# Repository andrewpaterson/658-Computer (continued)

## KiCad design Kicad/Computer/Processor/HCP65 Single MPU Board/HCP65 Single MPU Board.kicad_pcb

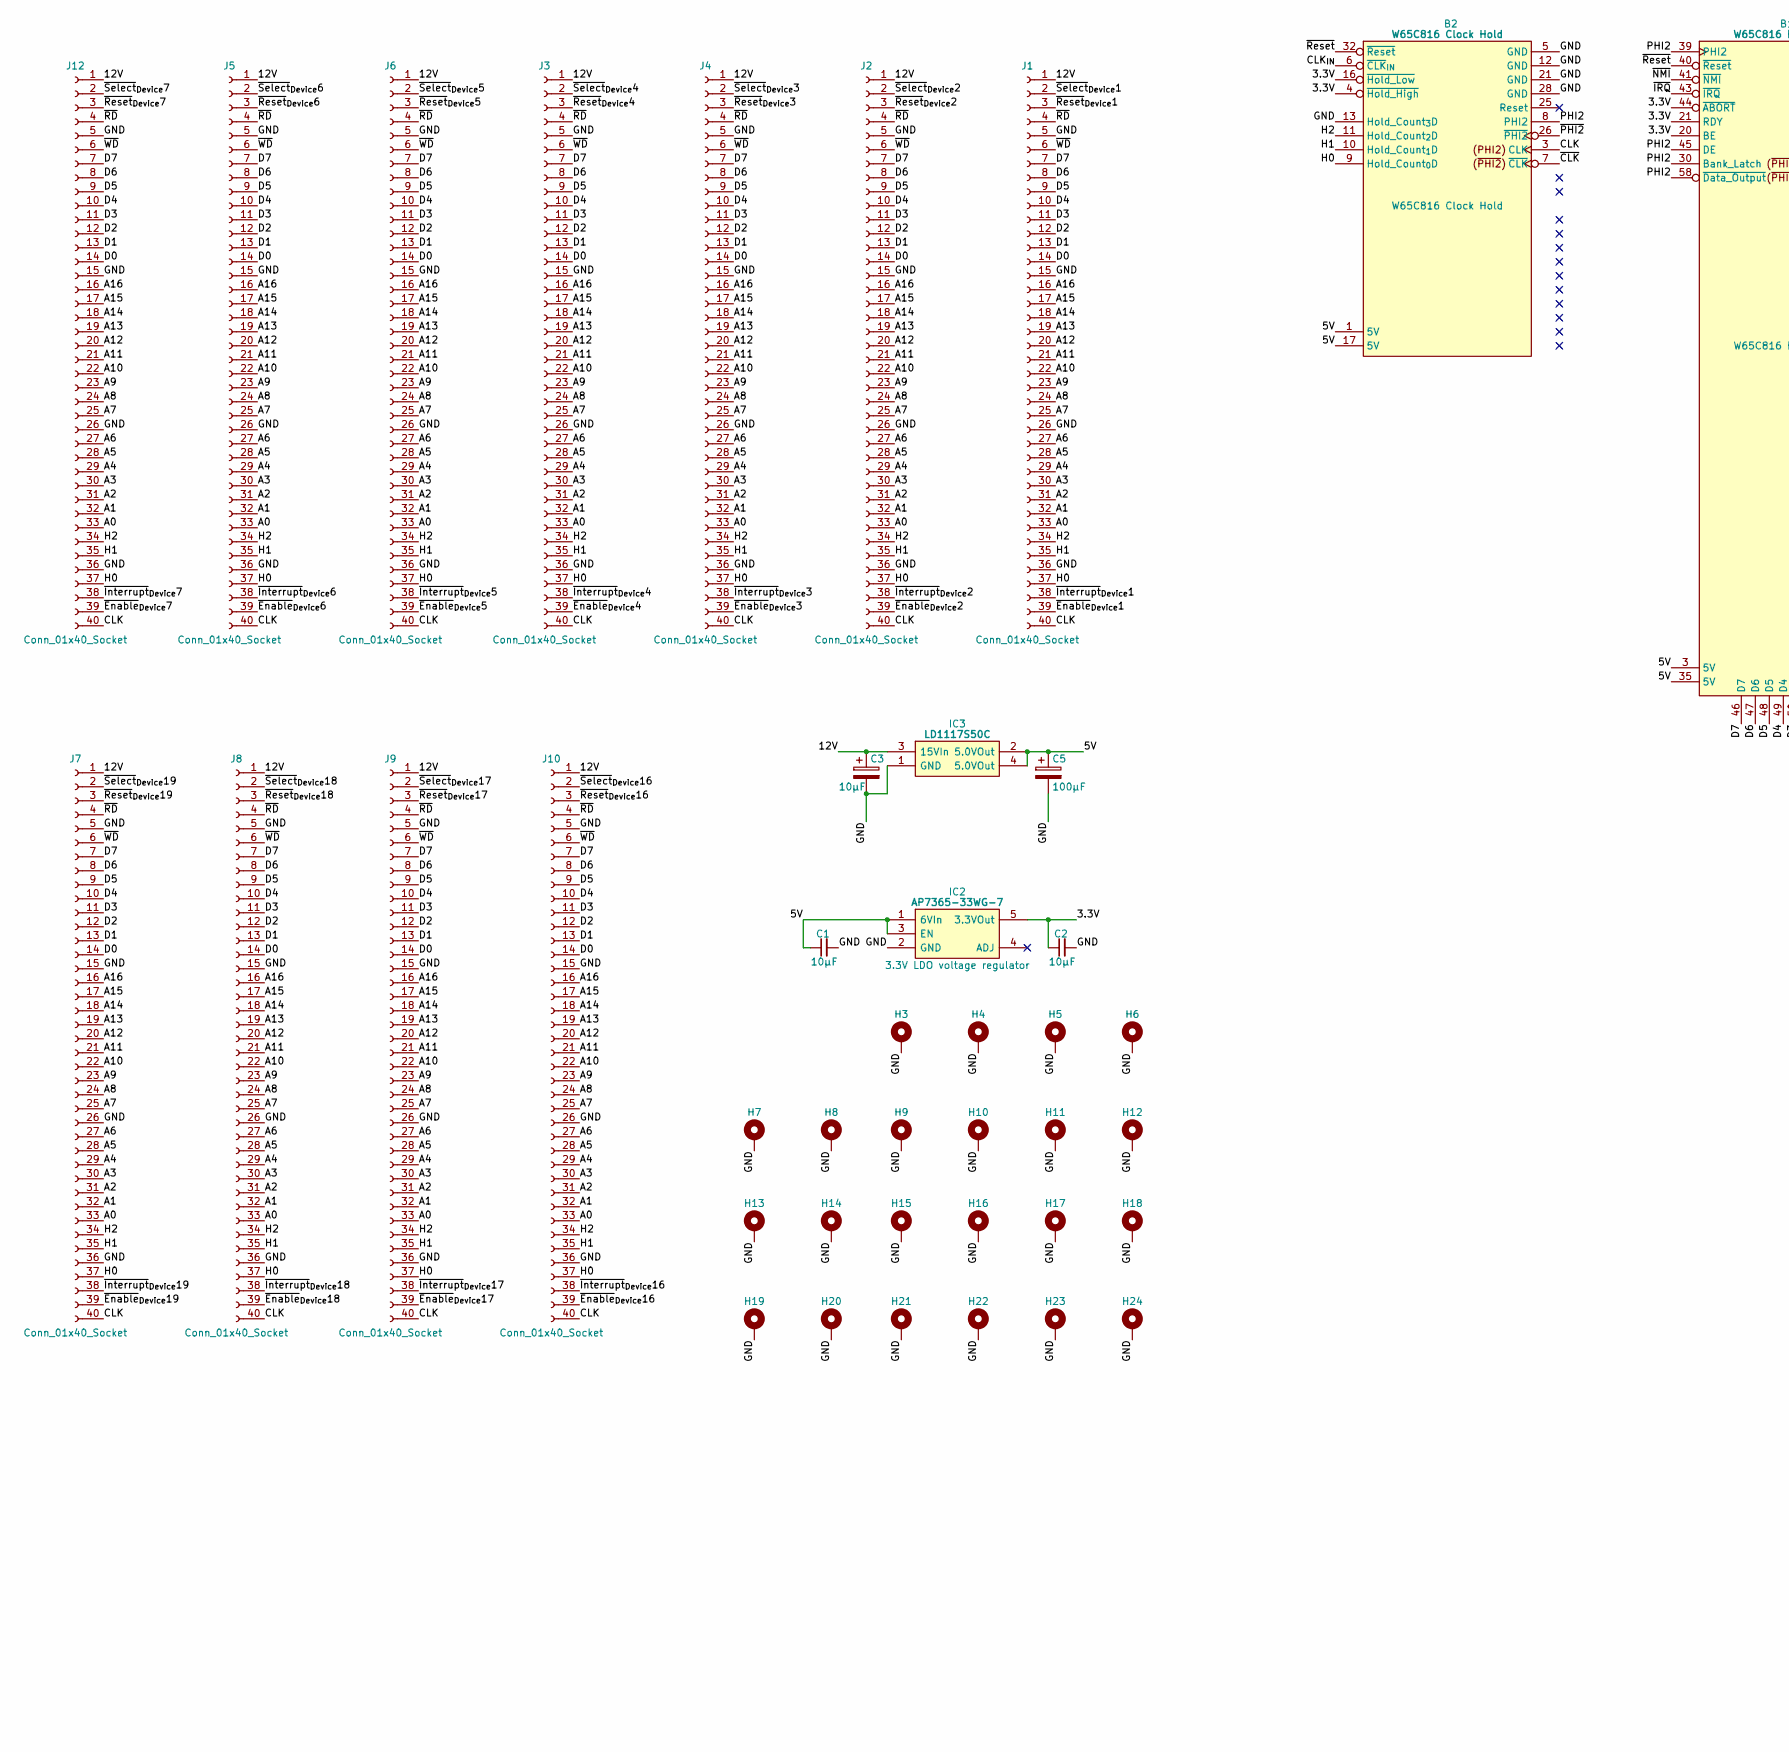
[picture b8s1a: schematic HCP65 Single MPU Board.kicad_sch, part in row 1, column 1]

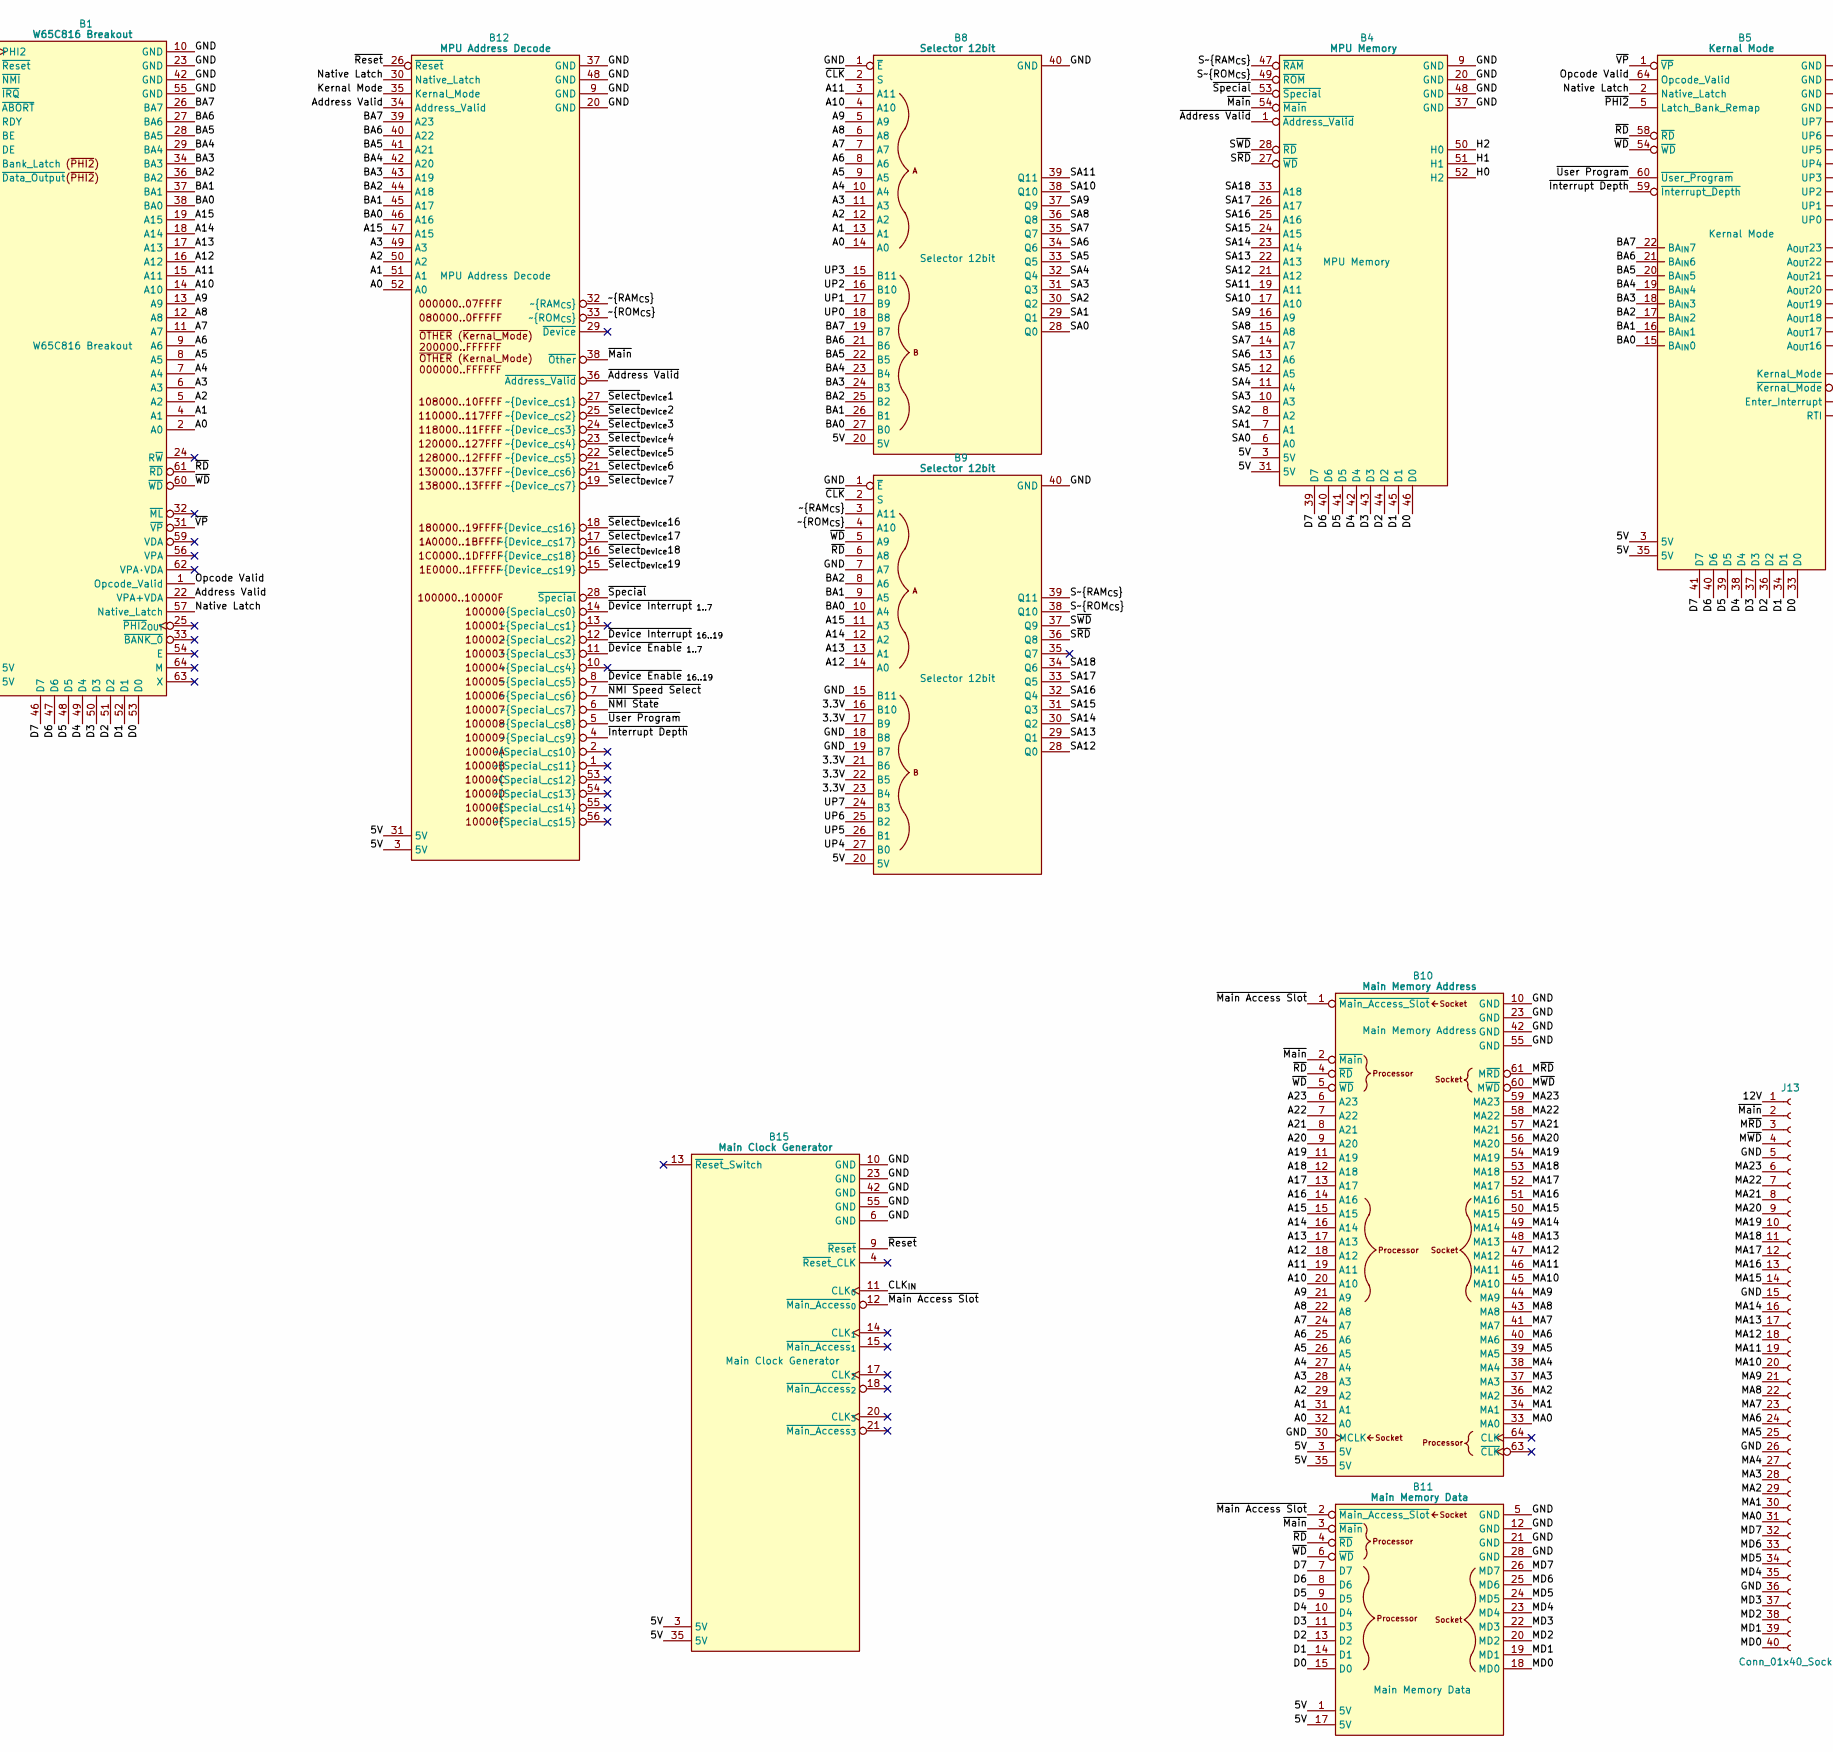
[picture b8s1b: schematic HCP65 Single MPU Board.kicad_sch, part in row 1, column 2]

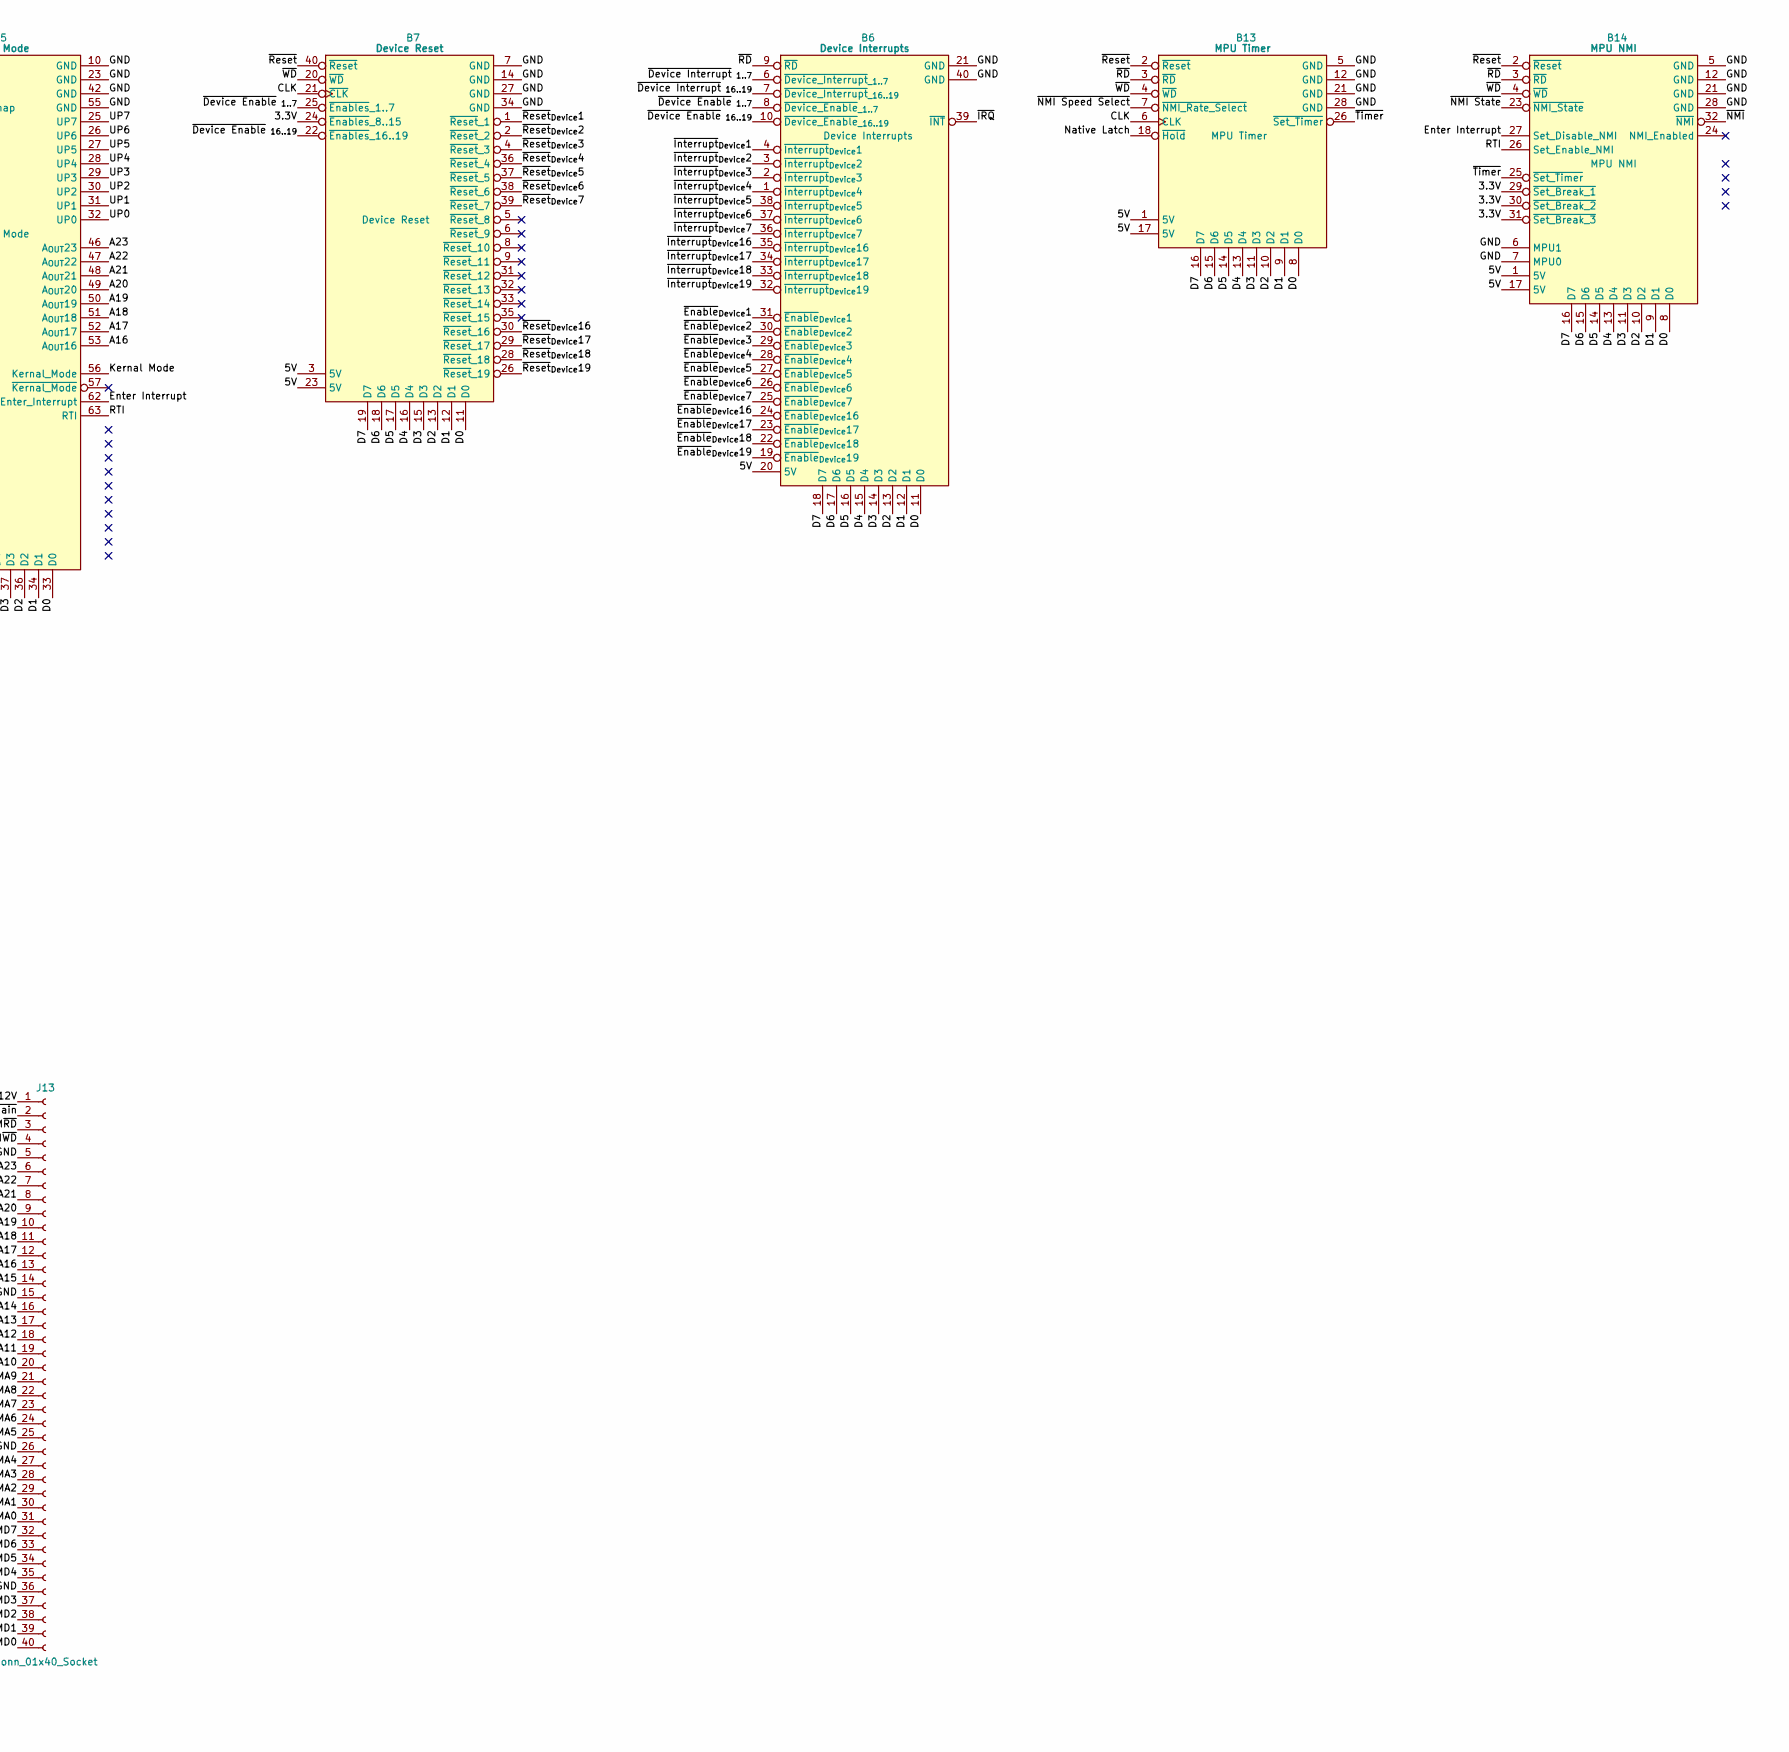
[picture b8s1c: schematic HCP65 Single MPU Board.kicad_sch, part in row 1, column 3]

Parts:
B1: W65C816 Breakout; HCP65_W65C816_Breakout
B2: W65C816 Clock Hold; HCP65_W65C816_Clock_Hold
B4: MPU Memory; HCP65_MPU_Memory
B5: Kernal Mode; HCP65_Kernal_Mode
B6: Device Interrupts; HCP65_Device_Interrupts
B7: Device Reset; HCP65_Device_Reset
B8, B9: Selector 12bit; HCP65_Selector_12bit
B10: Main Memory Address; HCP65_Main_Memory_Address
B11: Main Memory Data; HCP65_Main_Memory_Data
B12: MPU Address Decode; HCP65_MPU_Address_Decode
B13: MPU Timer; HCP65_MPU_Timer
B14: MPU NMI; HCP65_MPU_NMI
B15: Main Clock Generator; HCP65_Clock_Generator
C1, C2: 10µF; C_0805
C3: 10μF; CP_Radial_D4.0mm_P2.00mm
C5: 100μF; CP_Radial_D4.0mm_P2.00mm
H3, H4, H5, H6, H7, H8, H9, H10, H11, H12, H13, H14, H15, H16, H17, H18, H19, H20, H21, H22, H23, H24: MountingHole_Pad; HCP65_MountingHole_M3_
IC2: AP7365-33WG-7; SOT95P285X130-5N; Manufacturer_Part_Number AP7365-33WG-7; Mouser Part Number 621-AP7365-33WG-7
IC3: LD1117S50C; LD1117S33C; Manufacturer_Part_Number LD1117S50C
J1, J2, J3, J4, J5, J6, J7, J8, J9, J10, J12, J13: Conn_01x40_Socket

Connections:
/3.3V: B1.20 (BE), B1.21 (RDY), B1.44 (~ABORT), B2.4 (~Hold_High), B2.16 (~Hold_Low), B7.24 (~Enables_8..15), B9.16 (B10), B9.17 (B9), B9.21 (B6), B9.22 (B5), B9.23 (B4), B14.29 (~Set_Break_1), B14.30 (~Set_Break_2), B14.31 (~Set_Break_3), C2.1, IC2.5 (3.3VOut)
/5V: B1.3 (5V), B1.35 (5V), B2.1 (5V), B2.17 (5V), B4.3 (5V), B4.31 (5V), B5.3 (5V), B5.35 (5V), B6.20 (5V), B7.3 (5V), B7.23 (5V), B8.20 (5V), B9.20 (5V), B10.3 (5V), B10.35 (5V), B11.1 (5V), B11.17 (5V), B12.3 (5V), B12.31 (5V), B13.1 (5V), B13.17 (5V), B14.1 (5V), B14.17 (5V), B15.3 (5V), B15.35 (5V), C1.1, C5.1, IC2.1 (6VIn), IC2.3 (EN), IC3.2 (5.0VOut), IC3.4 (5.0VOut)
/12V: C3.1, IC3.3 (15VIn), J1.1, J2.1, J3.1, J4.1, J5.1, J6.1, J7.1, J8.1, J9.1, J10.1, J12.1, J13.1
/A0: B1.2 (A0), B8.14 (A0), B10.32 (A0), B12.52 (A0), J1.33, J2.33, J3.33, J4.33, J5.33, J6.33, J7.33, J8.33, J9.33, J10.33, J12.33
/A1: B1.4 (A1), B8.13 (A1), B10.31 (A1), B12.51 (A1), J1.32, J2.32, J3.32, J4.32, J5.32, J6.32, J7.32, J8.32, J9.32, J10.32, J12.32
/A2: B1.5 (A2), B8.12 (A2), B10.29 (A2), B12.50 (A2), J1.31, J2.31, J3.31, J4.31, J5.31, J6.31, J7.31, J8.31, J9.31, J10.31, J12.31
/A3: B1.6 (A3), B8.11 (A3), B10.28 (A3), B12.49 (A3), J1.30, J2.30, J3.30, J4.30, J5.30, J6.30, J7.30, J8.30, J9.30, J10.30, J12.30
/A4: B1.7 (A4), B8.10 (A4), B10.27 (A4), J1.29, J2.29, J3.29, J4.29, J5.29, J6.29, J7.29, J8.29, J9.29, J10.29, J12.29
/A5: B1.8 (A5), B8.9 (A5), B10.26 (A5), J1.28, J2.28, J3.28, J4.28, J5.28, J6.28, J7.28, J8.28, J9.28, J10.28, J12.28
/A6: B1.9 (A6), B8.8 (A6), B10.25 (A6), J1.27, J2.27, J3.27, J4.27, J5.27, J6.27, J7.27, J8.27, J9.27, J10.27, J12.27
/A7: B1.11 (A7), B8.7 (A7), B10.24 (A7), J1.25, J2.25, J3.25, J4.25, J5.25, J6.25, J7.25, J8.25, J9.25, J10.25, J12.25
/A8: B1.12 (A8), B8.6 (A8), B10.22 (A8), J1.24, J2.24, J3.24, J4.24, J5.24, J6.24, J7.24, J8.24, J9.24, J10.24, J12.24
/A9: B1.13 (A9), B8.5 (A9), B10.21 (A9), J1.23, J2.23, J3.23, J4.23, J5.23, J6.23, J7.23, J8.23, J9.23, J10.23, J12.23
/A10: B1.14 (A10), B8.4 (A10), B10.20 (A10), J1.22, J2.22, J3.22, J4.22, J5.22, J6.22, J7.22, J8.22, J9.22, J10.22, J12.22
/A11: B1.15 (A11), B8.3 (A11), B10.19 (A11), J1.21, J2.21, J3.21, J4.21, J5.21, J6.21, J7.21, J8.21, J9.21, J10.21, J12.21
/A12: B1.16 (A12), B9.14 (A0), B10.18 (A12), J1.20, J2.20, J3.20, J4.20, J5.20, J6.20, J7.20, J8.20, J9.20, J10.20, J12.20
/A13: B1.17 (A13), B9.13 (A1), B10.17 (A13), J1.19, J2.19, J3.19, J4.19, J5.19, J6.19, J7.19, J8.19, J9.19, J10.19, J12.19
/A14: B1.18 (A14), B9.12 (A2), B10.16 (A14), J1.18, J2.18, J3.18, J4.18, J5.18, J6.18, J7.18, J8.18, J9.18, J10.18, J12.18
/A15: B1.19 (A15), B9.11 (A3), B10.15 (A15), B12.47 (A15), J1.17, J2.17, J3.17, J4.17, J5.17, J6.17, J7.17, J8.17, J9.17, J10.17, J12.17
/A16: B5.53 (A_{OUT}16), B10.14 (A16), J1.16, J2.16, J3.16, J4.16, J5.16, J6.16, J7.16, J8.16, J9.16, J10.16, J12.16
/A17: B5.52 (A_{OUT}17), B10.13 (A17)
/A18: B5.51 (A_{OUT}18), B10.12 (A18)
/A19: B5.50 (A_{OUT}19), B10.11 (A19)
/A20: B5.49 (A_{OUT}20), B10.9 (A20)
/A21: B5.48 (A_{OUT}21), B10.8 (A21)
/A22: B5.47 (A_{OUT}22), B10.7 (A22)
/A23: B5.46 (A_{OUT}23), B10.6 (A23)
/Address Valid: B1.22 (VPA+VDA), B12.34 (Address_Valid)
/BA0: B1.38 (BA0), B5.15 (BA_{IN}0), B8.27 (B0), B9.10 (A4), B12.46 (A16)
/BA1: B1.37 (BA1), B5.16 (BA_{IN}1), B8.26 (B1), B9.9 (A5), B12.45 (A17)
/BA2: B1.36 (BA2), B5.17 (BA_{IN}2), B8.25 (B2), B9.8 (A6), B12.44 (A18)
/BA3: B1.34 (BA3), B5.18 (BA_{IN}3), B8.24 (B3), B12.43 (A19)
/BA4: B1.29 (BA4), B5.19 (BA_{IN}4), B8.23 (B4), B12.42 (A20)
/BA5: B1.28 (BA5), B5.20 (BA_{IN}5), B8.22 (B5), B12.41 (A21)
/BA6: B1.27 (BA6), B5.21 (BA_{IN}6), B8.21 (B6), B12.40 (A22)
/BA7: B1.26 (BA7), B5.22 (BA_{IN}7), B8.19 (B7), B12.39 (A23)
/CLK: B2.3 (CLK), B7.21 (~CLK), B13.6 (CLK), J1.40, J2.40, J3.40, J4.40, J5.40, J6.40, J7.40, J8.40, J9.40, J10.40, J12.40
/CLK_{IN}: B2.6 (~CLK_{IN}), B15.11 (CLK_{0})
/D0: B1.53 (D0), B4.46 (D0), B5.33 (D0), B6.11 (D0), B7.11 (D0), B11.15 (D0), B13.8 (D0), B14.8 (D0), J1.14, J2.14, J3.14, J4.14, J5.14, J6.14, J7.14, J8.14, J9.14, J10.14, J12.14
/D1: B1.52 (D1), B4.45 (D1), B5.34 (D1), B6.12 (D1), B7.12 (D1), B11.14 (D1), B13.9 (D1), B14.9 (D1), J1.13, J2.13, J3.13, J4.13, J5.13, J6.13, J7.13, J8.13, J9.13, J10.13, J12.13
/D2: B1.51 (D2), B4.44 (D2), B5.36 (D2), B6.13 (D2), B7.13 (D2), B11.13 (D2), B13.10 (D2), B14.10 (D2), J1.12, J2.12, J3.12, J4.12, J5.12, J6.12, J7.12, J8.12, J9.12, J10.12, J12.12
/D3: B1.50 (D3), B4.43 (D3), B5.37 (D3), B6.14 (D3), B7.15 (D3), B11.11 (D3), B13.11 (D3), B14.11 (D3), J1.11, J2.11, J3.11, J4.11, J5.11, J6.11, J7.11, J8.11, J9.11, J10.11, J12.11
/D4: B1.49 (D4), B4.42 (D4), B5.38 (D4), B6.15 (D4), B7.16 (D4), B11.10 (D4), B13.13 (D4), B14.13 (D4), J1.10, J2.10, J3.10, J4.10, J5.10, J6.10, J7.10, J8.10, J9.10, J10.10, J12.10
/D5: B1.48 (D5), B4.41 (D5), B5.39 (D5), B6.16 (D5), B7.17 (D5), B11.9 (D5), B13.14 (D5), B14.14 (D5), J1.9, J2.9, J3.9, J4.9, J5.9, J6.9, J7.9, J8.9, J9.9, J10.9, J12.9
/D6: B1.47 (D6), B4.40 (D6), B5.40 (D6), B6.17 (D6), B7.18 (D6), B11.8 (D6), B13.15 (D6), B14.15 (D6), J1.8, J2.8, J3.8, J4.8, J5.8, J6.8, J7.8, J8.8, J9.8, J10.8, J12.8
/D7: B1.46 (D7), B4.39 (D7), B5.41 (D7), B6.18 (D7), B7.19 (D7), B11.7 (D7), B13.16 (D7), B14.16 (D7), J1.7, J2.7, J3.7, J4.7, J5.7, J6.7, J7.7, J8.7, J9.7, J10.7, J12.7
/Enter Interrupt: B5.62 (Enter_Interrupt), B14.27 (Set_Disable_NMI)
/GND: B1.10 (GND), B1.23 (GND), B1.42 (GND), B1.55 (GND), B2.5 (GND), B2.12 (GND), B2.13 (Hold_Count_{3}D), B2.21 (GND), B2.28 (GND), B4.9 (GND), B4.20 (GND), B4.37 (GND), B4.48 (GND), B5.10 (GND), B5.23 (GND), B5.42 (GND), B5.55 (GND), B6.21 (GND), B6.40 (GND), B7.7 (GND), B7.14 (GND), B7.27 (GND), B7.34 (GND), B8.1 (~E), B8.40 (GND), B9.1 (~E), B9.7 (A7), B9.15 (B11), B9.18 (B8), B9.19 (B7), B9.40 (GND), B10.10 (GND), B10.23 (GND), B10.30 (MCLK), B10.42 (GND), B10.55 (GND), B11.5 (GND), B11.12 (GND), B11.21 (GND), B11.28 (GND), B12.9 (GND), B12.20 (GND), B12.37 (GND), B12.48 (GND), B13.5 (GND), B13.12 (GND), B13.21 (GND), B13.28 (GND), B14.5 (GND), B14.6 (MPU1), B14.7 (MPU0), B14.12 (GND), B14.21 (GND), B14.28 (GND), B15.6 (GND), B15.10 (GND), B15.23 (GND), B15.42 (GND), B15.55 (GND), C1.2, C2.2, C3.2, C5.2, H3.1 (GND), H4.1 (GND), H5.1 (GND), H6.1 (GND), H7.1 (GND), H8.1 (GND), H9.1 (GND), H10.1 (GND), H11.1 (GND), H12.1 (GND), H13.1 (GND), H14.1 (GND), H15.1 (GND), H16.1 (GND), H17.1 (GND), H18.1 (GND), H19.1 (GND), H20.1 (GND), H21.1 (GND), H22.1 (GND), H23.1 (GND), H24.1 (GND), IC2.2 (GND), IC3.1 (GND), J1.5, J1.15, J1.26, J1.36, J2.5, J2.15, J2.26, J2.36, J3.5, J3.15, J3.26, J3.36, J4.5, J4.15, J4.26, J4.36, J5.5, J5.15, J5.26, J5.36, J6.5, J6.15, J6.26, J6.36, J7.5, J7.15, J7.26, J7.36, J8.5, J8.15, J8.26, J8.36, J9.5, J9.15, J9.26, J9.36, J10.5, J10.15, J10.26, J10.36, J12.5, J12.15, J12.26, J12.36, J13.5, J13.15, J13.26, J13.36
/H0: B2.9 (Hold_Count_{0}D), B4.52 (H2), J1.37, J2.37, J3.37, J4.37, J5.37, J6.37, J7.37, J8.37, J9.37, J10.37, J12.37
/H1: B2.10 (Hold_Count_{1}D), B4.51 (H1), J1.35, J2.35, J3.35, J4.35, J5.35, J6.35, J7.35, J8.35, J9.35, J10.35, J12.35
/H2: B2.11 (Hold_Count_{2}D), B4.50 (H0), J1.34, J2.34, J3.34, J4.34, J5.34, J6.34, J7.34, J8.34, J9.34, J10.34, J12.34
/Kernal Mode: B5.56 (Kernal_Mode), B12.35 (Kernal_Mode)
/MA0: B10.33 (MA0), J13.31
/MA1: B10.34 (MA1), J13.30
/MA2: B10.36 (MA2), J13.29
/MA3: B10.37 (MA3), J13.28
/MA4: B10.38 (MA4), J13.27
/MA5: B10.39 (MA5), J13.25
/MA6: B10.40 (MA6), J13.24
/MA7: B10.41 (MA7), J13.23
/MA8: B10.43 (MA8), J13.22
/MA9: B10.44 (MA9), J13.21
/MA10: B10.45 (MA10), J13.20
/MA11: B10.46 (MA11), J13.19
/MA12: B10.47 (MA12), J13.18
/MA13: B10.48 (MA13), J13.17
/MA14: B10.49 (MA14), J13.16
/MA15: B10.50 (MA15), J13.14
/MA16: B10.51 (MA16), J13.13
/MA17: B10.52 (MA17), J13.12
/MA18: B10.53 (MA18), J13.11
/MA19: B10.54 (MA19), J13.10
/MA20: B10.56 (MA20), J13.9
/MA21: B10.57 (MA21), J13.8
/MA22: B10.58 (MA22), J13.7
/MA23: B10.59 (MA23), J13.6
/MD0: B11.18 (MD0), J13.40
/MD1: B11.19 (MD1), J13.39
/MD2: B11.20 (MD2), J13.38
/MD3: B11.22 (MD3), J13.37
/MD4: B11.23 (MD4), J13.35
/MD5: B11.24 (MD5), J13.34
/MD6: B11.25 (MD6), J13.33
/MD7: B11.26 (MD7), J13.32
/M~RD: B10.61 (M~RD), J13.3
/M~WD: B10.60 (M~WD), J13.4
/Native Latch: B1.57 (Native_Latch), B5.2 (Native_Latch), B12.30 (Native_Latch), B13.18 (~Hold)
/Opcode Valid: B1.1 (Opcode_Valid), B5.64 (Opcode_Valid)
/PHI2: B1.30 (Bank_Latch), B1.39 (PHI2), B1.45 (DE), B1.58 (~Data_Output), B2.8 (PHI2)
/RTI: B5.63 (RTI), B14.26 (Set_Enable_NMI)
/SA0: B4.6 (A0), B8.28 (Q0)
/SA1: B4.7 (A1), B8.29 (Q1)
/SA2: B4.8 (A2), B8.30 (Q2)
/SA3: B4.10 (A3), B8.31 (Q3)
/SA4: B4.11 (A4), B8.32 (Q4)
/SA5: B4.12 (A5), B8.33 (Q5)
/SA6: B4.13 (A6), B8.34 (Q6)
/SA7: B4.14 (A7), B8.35 (Q7)
/SA8: B4.15 (A8), B8.36 (Q8)
/SA9: B4.16 (A9), B8.37 (Q9)
/SA10: B4.17 (A10), B8.38 (Q10)
/SA11: B4.19 (A11), B8.39 (Q11)
/SA12: B4.21 (A12), B9.28 (Q0)
/SA13: B4.22 (A13), B9.29 (Q1)
/SA14: B4.23 (A14), B9.30 (Q2)
/SA15: B4.24 (A15), B9.31 (Q3)
/SA16: B4.25 (A16), B9.32 (Q4)
/SA17: B4.26 (A17), B9.33 (Q5)
/SA18: B4.33 (A18), B9.34 (Q6)
/S~RAM_{CS}: B4.47 (~RAM), B9.39 (Q11)
/S~RD: B4.27 (~WD), B9.36 (Q8)
/S~ROM_{CS}: B4.49 (~ROM), B9.38 (Q10)
/S~WD: B4.28 (~RD), B9.37 (Q9)
/UP0: B5.32 (UP0), B8.18 (B8)
/UP1: B5.31 (UP1), B8.17 (B9)
/UP2: B5.30 (UP2), B8.16 (B10)
/UP3: B5.29 (UP3), B8.15 (B11)
/UP4: B5.28 (UP4), B9.27 (B0)
/UP5: B5.27 (UP5), B9.26 (B1)
/UP6: B5.26 (UP6), B9.25 (B2)
/UP7: B5.25 (UP7), B9.24 (B3)
/~Address Valid: B4.1 (~Address_Valid), B12.36 (~Address_Valid)
/~CLK: B2.7 (~CLK), B8.2 (S), B9.2 (S)
/~Device Enable_{ 1..7}: B6.8 (~Device_Enable_{_1..7}), B7.25 (~Enables_1..7), B12.11 (~Special__{CS3})
/~Device Enable_{ 16..19}: B6.10 (~Device_Enable_{_16..19}), B7.22 (~Enables_16..19), B12.8 (~Special__{CS5})
/~Device Interrupt_{ 1..7}: B6.6 (~Device_Interrupt_{_1..7}), B12.14 (~Special__{CS0})
/~Device Interrupt_{ 16..19}: B6.7 (~Device_Interrupt_{_16..19}), B12.12 (~Special__{CS2})
/~Enable_{Device}1: B6.31 (~Enable_{Device}1), J1.39
/~Enable_{Device}2: B6.30 (~Enable_{Device}2), J2.39
/~Enable_{Device}3: B6.29 (~Enable_{Device}3), J4.39
/~Enable_{Device}4: B6.28 (~Enable_{Device}4), J3.39
/~Enable_{Device}5: B6.27 (~Enable_{Device}5), J6.39
/~Enable_{Device}6: B6.26 (~Enable_{Device}6), J5.39
/~Enable_{Device}7: B6.25 (~Enable_{Device}7), J12.39
/~Enable_{Device}16: B6.24 (~Enable_{Device}16), J10.39
/~Enable_{Device}17: B6.23 (~Enable_{Device}17), J9.39
/~Enable_{Device}18: B6.22 (~Enable_{Device}18), J8.39
/~Enable_{Device}19: B6.19 (~Enable_{Device}19), J7.39
/~IRQ: B1.43 (~IRQ), B6.39 (~INT)
/~Interrupt Depth: B5.59 (~Interrupt_Depth), B12.4 (~Special__{CS9})
/~Interrupt_{Device}1: B6.4 (~Interrupt_{Device}1), J1.38
/~Interrupt_{Device}2: B6.3 (~Interrupt_{Device}2), J2.38
/~Interrupt_{Device}3: B6.2 (~Interrupt_{Device}3), J4.38
/~Interrupt_{Device}4: B6.1 (~Interrupt_{Device}4), J3.38
/~Interrupt_{Device}5: B6.38 (~Interrupt_{Device}5), J6.38
/~Interrupt_{Device}6: B6.37 (~Interrupt_{Device}6), J5.38
/~Interrupt_{Device}7: B6.36 (~Interrupt_{Device}7), J12.38
/~Interrupt_{Device}16: B6.35 (~Interrupt_{Device}16), J10.38
/~Interrupt_{Device}17: B6.34 (~Interrupt_{Device}17), J9.38
/~Interrupt_{Device}18: B6.33 (~Interrupt_{Device}18), J8.38
/~Interrupt_{Device}19: B6.32 (~Interrupt_{Device}19), J7.38
/~Main Access Slot: B10.1 (~Main_Access_Slot), B11.2 (~Main_Access_Slot), B15.12 (~Main_Access_{0})
/~Main: B4.54 (~Main), B10.2 (~Main), B11.3 (~Main), B12.38 (~Other), J13.2
/~NMI Speed Select: B12.7 (~Special__{CS6}), B13.7 (~NMI_Rate_Select)
/~NMI State: B12.6 (~Special__{CS7}), B14.23 (~NMI_State)
/~NMI: B1.41 (~NMI), B14.32 (~NMI)
/~PHI2: B2.26 (~PHI2), B5.5 (Latch_Bank_Remap)
/~RAM_{CS}: B9.3 (A11), B12.32 (~RAM_{CS})
/~RD: B1.61 (~RD), B5.58 (~RD), B6.9 (~RD), B9.6 (A8), B10.4 (~RD), B11.4 (~RD), B13.3 (~RD), B14.3 (~RD), J1.4, J2.4, J3.4, J4.4, J5.4, J6.4, J7.4, J8.4, J9.4, J10.4, J12.4
/~ROM_{CS}: B9.4 (A10), B12.33 (~ROM_{CS})
/~Reset: B1.40 (~Reset), B2.32 (~Reset), B7.40 (~Reset), B12.26 (~Reset), B13.2 (~Reset), B14.2 (~Reset), B15.9 (~Reset)
/~Reset_{Device}1: B7.1 (~Reset_1), J1.3
/~Reset_{Device}2: B7.2 (~Reset_2), J2.3
/~Reset_{Device}3: B7.4 (~Reset_3), J4.3
/~Reset_{Device}4: B7.36 (~Reset_4), J3.3
/~Reset_{Device}5: B7.37 (~Reset_5), J6.3
/~Reset_{Device}6: B7.38 (~Reset_6), J5.3
/~Reset_{Device}7: B7.39 (~Reset_7), J12.3
/~Reset_{Device}16: B7.30 (~Reset_16), J10.3
/~Reset_{Device}17: B7.29 (~Reset_17), J9.3
/~Reset_{Device}18: B7.28 (~Reset_18), J8.3
/~Reset_{Device}19: B7.26 (~Reset_19), J7.3
/~Select_{Device}1: B12.27 (~Device__{CS1}), J1.2
/~Select_{Device}2: B12.25 (~Device__{CS2}), J2.2
/~Select_{Device}3: B12.24 (~Device__{CS3}), J4.2
/~Select_{Device}4: B12.23 (~Device__{CS4}), J3.2
/~Select_{Device}5: B12.22 (~Device__{CS5}), J6.2
/~Select_{Device}6: B12.21 (~Device__{CS6}), J5.2
/~Select_{Device}7: B12.19 (~Device__{CS7}), J12.2
/~Select_{Device}16: B12.18 (~Device__{CS16}), J10.2
/~Select_{Device}17: B12.17 (~Device__{CS17}), J9.2
/~Select_{Device}18: B12.16 (~Device__{CS18}), J8.2
/~Select_{Device}19: B12.15 (~Device__{CS19}), J7.2
/~Special: B4.53 (~Special), B12.28 (~Special)
/~Timer: B13.26 (~Set_Timer), B14.25 (~Set_Timer)
/~User Program: B5.60 (~User_Program), B12.5 (~Special__{CS8})
/~VP: B1.31 (~VP), B5.1 (~VP)
/~WD: B1.60 (~WD), B5.54 (~WD), B7.20 (~WD), B9.5 (A9), B10.5 (~WD), B11.6 (~WD), B13.4 (~WD), B14.4 (~WD), J1.6, J2.6, J3.6, J4.6, J5.6, J6.6, J7.6, J8.6, J9.6, J10.6, J12.6

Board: 2 copper layers, 54 parts (0 on the bottom side), 188 nets, no tracks yet.
